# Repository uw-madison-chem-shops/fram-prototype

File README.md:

# fram-prototype

Circuit demonstrating functionality of non-volatile, highly endurant ferroelectric RAM.

## Repository

This is an open source hardware project licensed under the CERN Open Hardware Licence Version 2 - Permissive.
Please see the LICENSE file for the complete license.

This repository is being mirrored to several version control systems in an attempt to ensure maximum avaliability.

| name           | url                                                     |
| -------------- | ------------------------------------------------------- | 
| Chem (primary) | https://git.chem.wisc.edu/shop/fram-prototype           |
| GitHub         | https://github.com/uw-madison-chem-shops/fram-prototype | 
| GitLab         | https://gitlab.com/uw-madison-chem-shops/fram-prototype |

## PCB

This PCB was designed using KiCAD version 5.
Refer to `fram-prototype.pdf` for schematic.
PCB images generated with [tracespace](https://github.com/tracespace/tracespace) follow.

## Bill of Materials

| reference      | value         | manufacturer  | part number          | vendors |
| :------------- | :------------ | :------------ | :------------------- | :------ |

## Firmware

TODO

## Changelog

### Revision A

#### Added
- initial design

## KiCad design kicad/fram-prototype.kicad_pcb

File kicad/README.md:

# fram-prototype

Circuit demonstrating functionality of non-volatile, highly endurant ferroelectric RAM.

## PCB

This PCB was designed using KiCAD version 5.
Refer to `fram-prototype.pdf` for schematic.
PCB images generated with [tracespace](https://github.com/tracespace/tracespace) follow.

Bill of Materials

| reference      | value         | manufacturer | part number          | vendors |
| :------------- | :------------ | :----------- | :------------------- | :------ | 
| U1             | FRAM 256K     | Fujitsu      | MB85RC256VFP-G-JNER2 | [DigiKey](https://www.digikey.com/en/products/detail/fujitsu-semiconductor/MB85RC256VPF-G-JNERE2/4022652) |

## Firmware

TODO

## Changelog

### 1.0.0

#### Added
- initial design

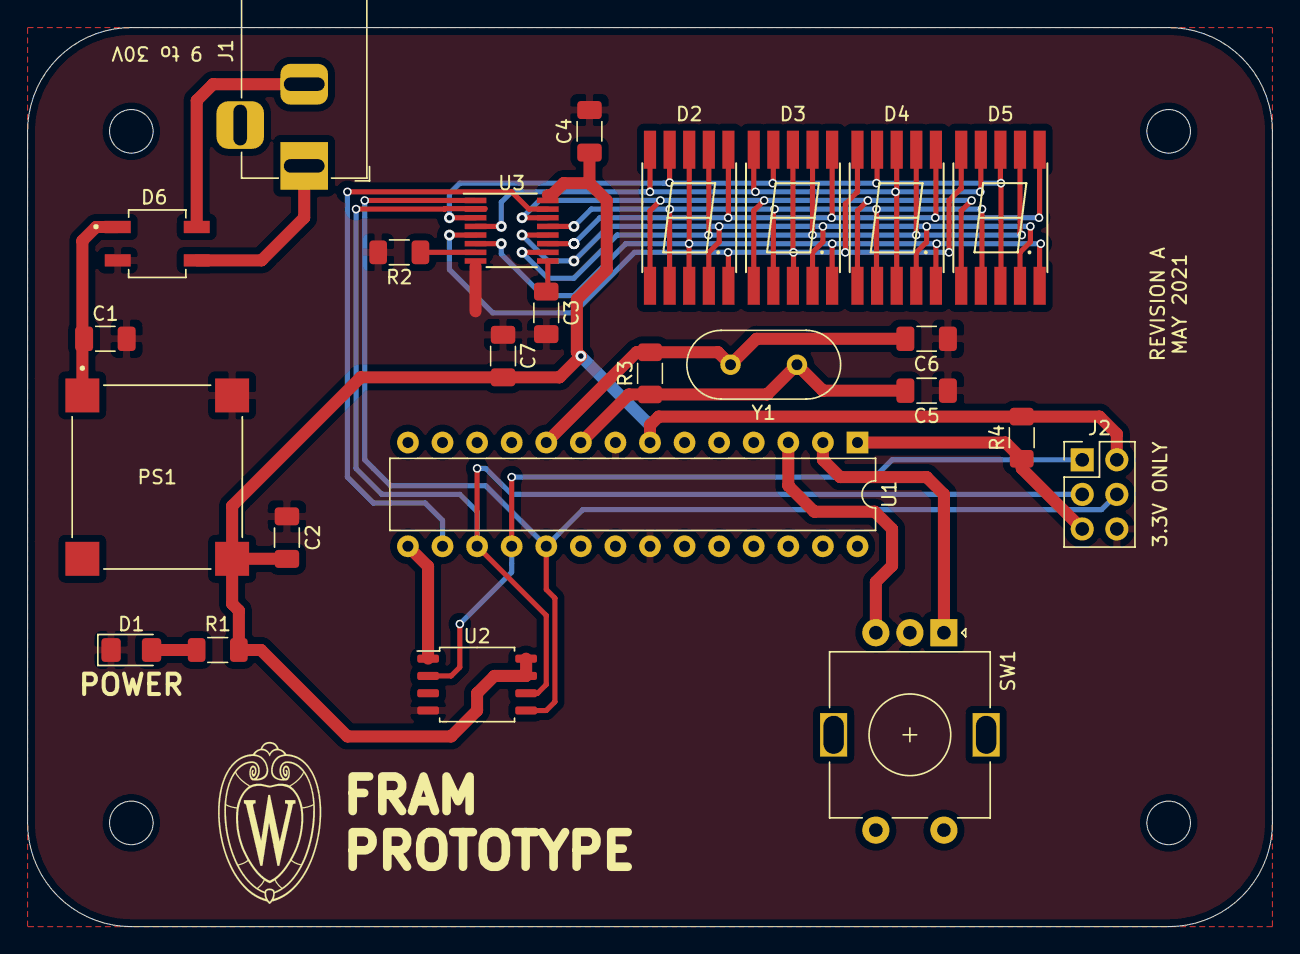
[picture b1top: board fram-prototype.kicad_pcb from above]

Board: 2 copper layers, 91.4 x 66.0 mm, 25 parts (0 on the bottom side), 27 nets.

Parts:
C1: 10u; C_1206_3216Metric_Pad1.33x1.80mm_HandSolder
C2: 22u; C_1206_3216Metric_Pad1.33x1.80mm_HandSolder
C3: C; C_1206_3216Metric_Pad1.33x1.80mm_HandSolder
C4, C7: 100n; C_1206_3216Metric_Pad1.33x1.80mm_HandSolder
C5, C6: 20p; C_1206_3216Metric_Pad1.33x1.80mm_HandSolder
D1: LED; LED_1206_3216Metric_Pad1.42x1.75mm_HandSolder
D2, D3, D4, D5: ACSC02-41SURKWA-F01
D6: CDBHM260L-HF; SOIC245P670X290-4N
J1: Barrel_Jack; BarrelJack_Horizontal
J2: AVR-ISP-6; PinHeader_2x03_P2.54mm_Vertical
PS1: VXO7803-500-M; CONV_VXO7805-500-M
R1: 100; R_1206_3216Metric_Pad1.30x1.75mm_HandSolder
R2: R_US; R_1206_3216Metric_Pad1.30x1.75mm_HandSolder
R3: 1M; R_1206_3216Metric_Pad1.30x1.75mm_HandSolder
R4: 4.7k; R_1206_3216Metric_Pad1.30x1.75mm_HandSolder
SW1: Rotary_Encoder_Switch; RotaryEncoder_Alps_EC11E-Switch_Vertical_H20mm
U1: ATmega328-PU; DIP-28_W7.62mm
U2: MB85RS256B; SOP-8_5.28x5.23mm_P1.27mm
U3: MAX6951; QSOP-16_3.9x4.9mm_P0.635mm
Y1: 8MHz; Crystal_HC49-U_Vertical

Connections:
+3V3: C2.1, C4.1, C7.2, J2.2, PS1.3, R1.1, R4.2, U1.7, U2.7, U2.8, U3.16
+VDC: C1.1, D6.1, PS1.1
/7seg/SEG0: D2.3, D2.8, D3.5, D4.5, D5.5, U3.6
/7seg/SEG1: D2.5, D3.3, D3.8, D4.10, D5.10, U3.5
/7seg/SEG2: D2.10, D3.10, D4.3, D4.8, D5.9, U3.4
/7seg/SEG3: D2.9, D3.9, D4.9, D5.3, D5.8, U3.3
/7seg/SEG4: D2.1, D3.1, D4.1, D5.1, U3.14
/7seg/SEG5: D2.2, D3.2, D4.2, D5.2, U3.13
/7seg/SEG6: D2.4, D3.4, D4.4, D5.4, U3.12
/7seg/SEG7: D2.6, D3.6, D4.6, D5.6, U3.11
/7seg/SEG8: D2.7, D3.7, D4.7, D5.7, U3.10
/7seg/~CS~: U1.16, U3.15
GND: C1.2, C2.2, C3.2, C4.2, C5.1, C6.1, C7.1, D1.1, D6.2, J2.6, PS1.2, R2.2, SW1.C, U1.8, U1.22, U2.4, U3.8
MISO: J2.1, U1.18, U2.2
MOSI: J2.4, U1.19, U2.5, U3.1
unnamed: C3.1, U3.9
unnamed: C5.2, R3.1, U1.9, Y1.1
unnamed: C6.2, R3.2, U1.10, Y1.2
unnamed: D1.2, R1.2
unnamed: D6.3, J1.1
unnamed: D6.4, J1.2
unnamed: J2.5, R4.1, U1.1
unnamed: R2.1, U3.7
unnamed: SW1.A, U1.2
unnamed: SW1.B, U1.3
unnamed: U1.15, U2.1
SCK: J2.3, U1.17, U2.6, U3.2

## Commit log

2021-01-25 readme changelog
2021-01-25 add fram part number
2021-01-27 first basic prototype
2021-03-25 restructure
2021-03-25 svgs
2021-05-03 revA
2021-05-03 revA-gerbers
